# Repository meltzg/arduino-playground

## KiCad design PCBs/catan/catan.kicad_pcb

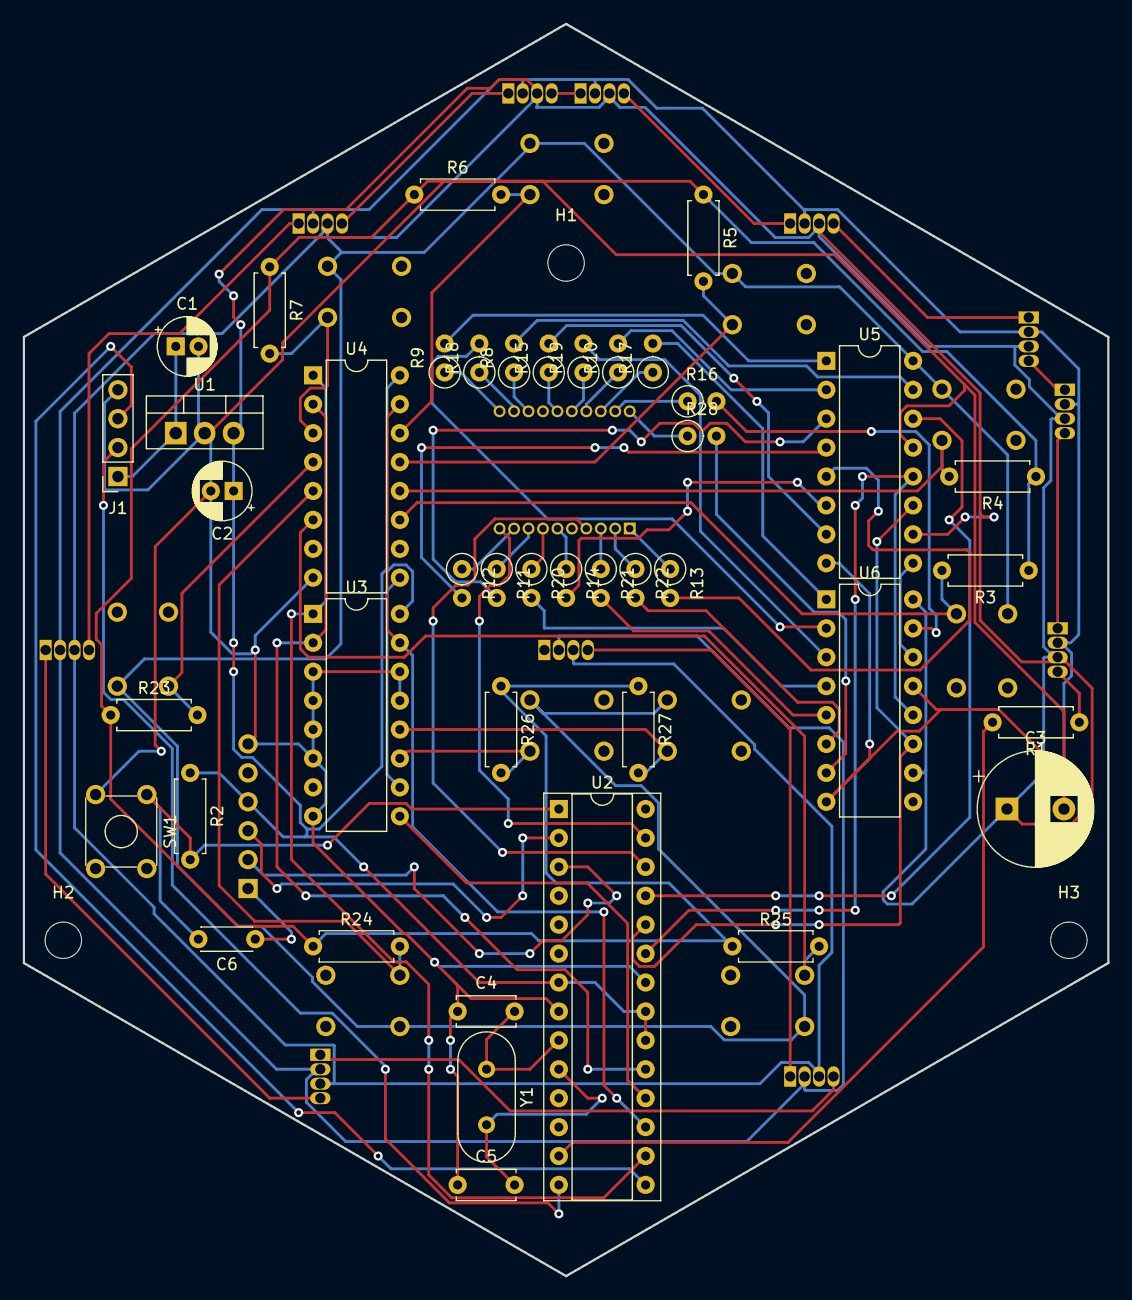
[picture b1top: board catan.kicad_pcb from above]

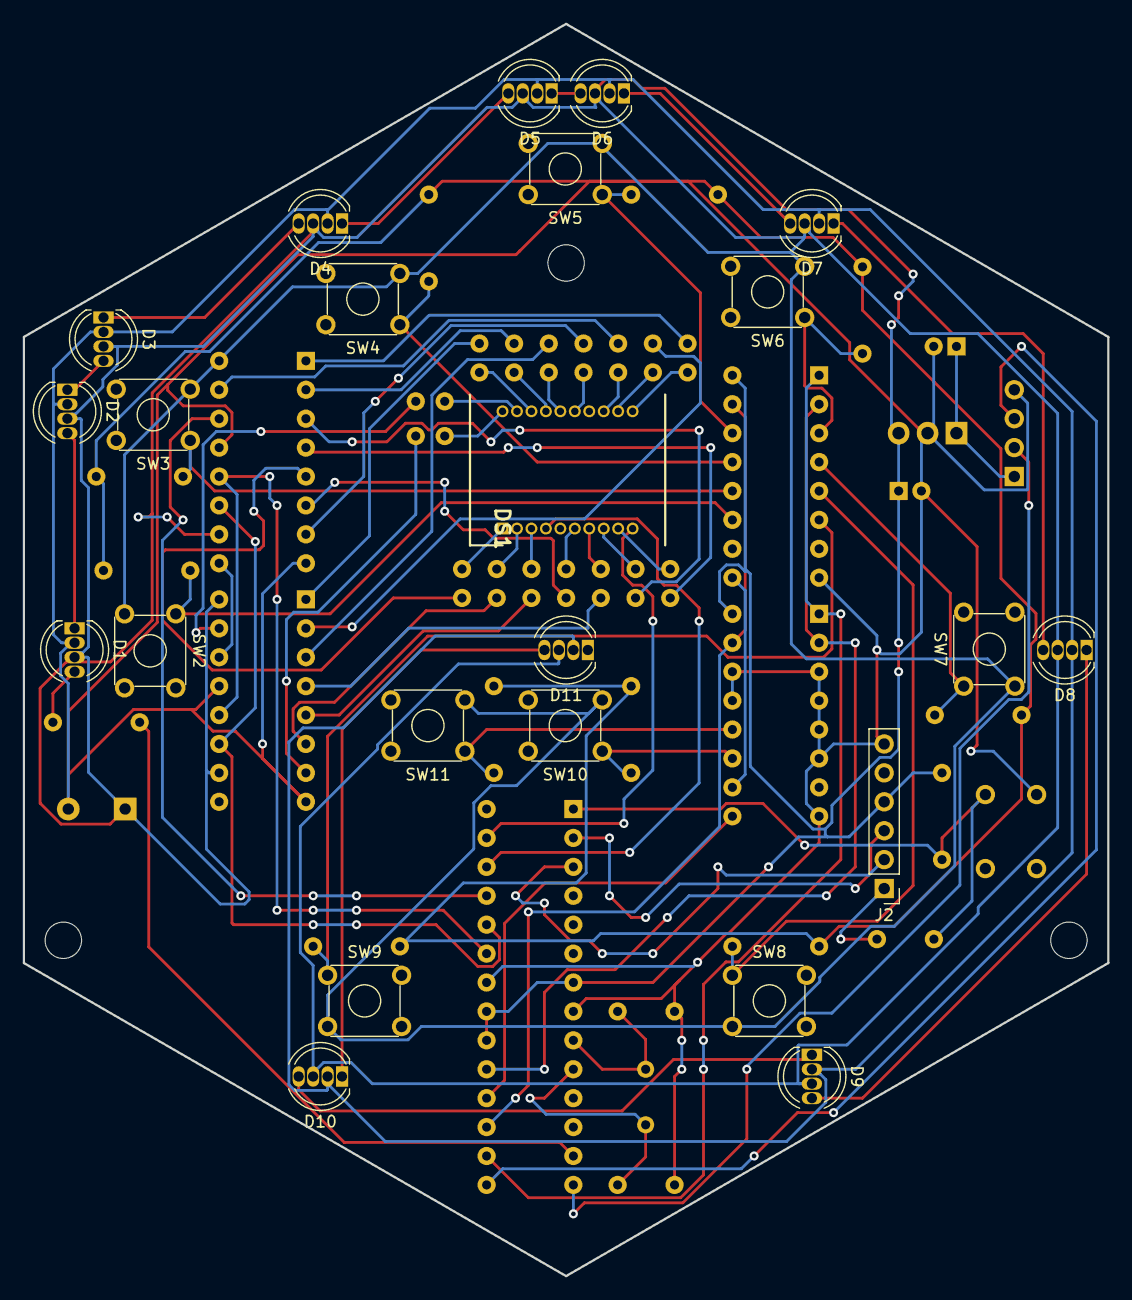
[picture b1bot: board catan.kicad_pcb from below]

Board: 2 copper layers, 95.3 x 110.0 mm, 69 parts (23 on the bottom side), 76 nets.

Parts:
C1, C2: CP1; CP_Radial_D5.0mm_P2.00mm
C3: CP1; CP_Radial_D10.0mm_P5.00mm
C4, C5: C_Small; C_Disc_D5.0mm_W2.5mm_P5.00mm
C6: C_Small; C_Disc_D4.3mm_W1.9mm_P5.00mm
D1, D2, D3, D4, D5, D6, D7, D8, D9, D10, D11: NeoPixel_THT; LED_D5.0mm-4_RGB
DS1: LTP-3862G; DIPS1030W45P127L1690H645Q20N
H1, H2, H3: MountingHole; MountingHole_3.2mm_M3
J1: Conn_01x04_Female; PinSocket_1x04_P2.54mm_Vertical
J2: Conn_01x06_Male; PinHeader_1x06_P2.54mm_Vertical
R1, R2, R3, R4, R5, R6, R7, R23, R24, R25, R26, R27: R; R_Axial_DIN0207_L6.3mm_D2.5mm_P7.62mm_Horizontal
R8, R9, R10, R11, R12, R13, R14, R15, R16, R17, R18, R19, R20, R21, R22, R28: R; R_Axial_DIN0207_L6.3mm_D2.5mm_P2.54mm_Vertical
SW1, SW2, SW3, SW4, SW5, SW6, SW7, SW8, SW9, SW10, SW11: SW_MEC_5E; SW_TH_Tactile_Omron_B3F-10xx
U1: LM7805_TO220; TO-220-3_Vertical
U2: ATmega328P-PU; DIP-28_W7.62mm_Socket
U3, U4: 74HC165; DIP-16_W7.62mm
U5, U6: 74HC595; DIP-16_W7.62mm
Y1: Crystal; Crystal_HC49-4H_Vertical

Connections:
+9V: C1.1, J1.1, U1.1
GND: C1.2, C2.2, C3.2, C4.1, C5.1, D1.2, D2.2, D3.2, D4.2, D5.2, D6.2, D7.2, D8.2, D9.2, D10.2, D11.2, J1.4, J2.6, R3.1, R4.1, R5.1, R6.1, R7.1, R23.1, R24.1, R25.1, R26.1, R27.1, SW1.3, U1.2, U2.8, U2.22, U3.3, U3.4, U3.5, U3.6, U3.8, U3.13, U3.14, U4.8, U5.8, U5.13, U6.8, U6.13
unnamed: C2.1, C3.1, D1.3, D2.3, D3.3, D4.3, D5.3, D6.3, D7.3, D8.3, D9.3, D10.3, D11.3, J2.4, R2.1, SW2.3, SW3.3, SW4.3, SW5.3, SW6.3, SW7.3, SW8.3, SW9.3, SW10.3, SW11.3, U1.3, U2.7, U2.20, U2.21, U3.16, U4.16, U5.10, U5.16, U6.10, U6.16
unnamed: C4.2, U2.9, Y1.1
unnamed: C5.2, U2.10, Y1.2
unnamed: C6.1, J2.1
unnamed: C6.2, R2.2, SW1.1, U2.1
unnamed: D1.1, D2.4
unnamed: D1.4, R1.1
unnamed: D2.1, D3.4
unnamed: D3.1, D4.4
unnamed: D4.1, D5.4
unnamed: D5.1, D6.4
unnamed: D6.1, D7.4
unnamed: D7.1, D8.4
unnamed: D8.1, D9.4
unnamed: D10.1, D11.4
unnamed: D9.1, D10.4
unnamed: DS1.1, R13.1
unnamed: DS1.2, R22.1
unnamed: DS1.3, R21.1
unnamed: DS1.4, U2.26
unnamed: DS1.6, R14.1
unnamed: DS1.7, R20.1
unnamed: DS1.8, R11.1
unnamed: DS1.9, R12.1
unnamed: DS1.10, U2.27
unnamed: DS1.11, R9.1
unnamed: DS1.12, R18.1
unnamed: DS1.13, R8.1
unnamed: DS1.15, R15.1
unnamed: DS1.16, R19.1
unnamed: DS1.17, R10.1
unnamed: DS1.18, R17.1
unnamed: DS1.19, R16.1
unnamed: DS1.20, R28.1
unnamed: J1.2, U2.14
unnamed: J1.3, U2.15
unnamed: J2.2, U2.3
unnamed: J2.3, U2.2
unnamed: R1.2, U2.13
unnamed: R3.2, SW2.1, U4.11
unnamed: R4.2, SW3.1, U4.12
unnamed: R5.2, SW4.1, U4.13
unnamed: R6.2, SW5.1, U4.14
unnamed: R7.2, SW6.1, U4.3
unnamed: R8.2, U5.15
unnamed: R9.2, U5.1
unnamed: R10.2, U5.2
unnamed: R11.2, U5.3
unnamed: R12.2, U5.4
unnamed: R13.2, U5.5
unnamed: R14.2, U5.6
unnamed: R15.2, U5.7
unnamed: R16.2, U6.15
unnamed: R17.2, U6.1
unnamed: R18.2, U6.2
unnamed: R19.2, U6.3
unnamed: R20.2, U6.4
unnamed: R21.2, U6.5
unnamed: R22.2, U6.6
unnamed: R23.2, SW7.1, U4.4
unnamed: R24.2, SW8.1, U4.5
unnamed: R25.2, SW9.1, U4.6
unnamed: R26.2, SW10.1, U3.11
unnamed: R27.2, SW11.1, U3.12
unnamed: R28.2, U6.7
unnamed: U2.16, U3.1, U4.1
unnamed: U2.17, U3.15, U4.15
unnamed: U2.18, U3.9
unnamed: U2.19, U3.2, U4.2
unnamed: U2.23, U5.12, U6.12
unnamed: U2.24, U5.11, U6.11
unnamed: U2.25, U5.14
unnamed: U3.10, U4.9
unnamed: U5.9, U6.14

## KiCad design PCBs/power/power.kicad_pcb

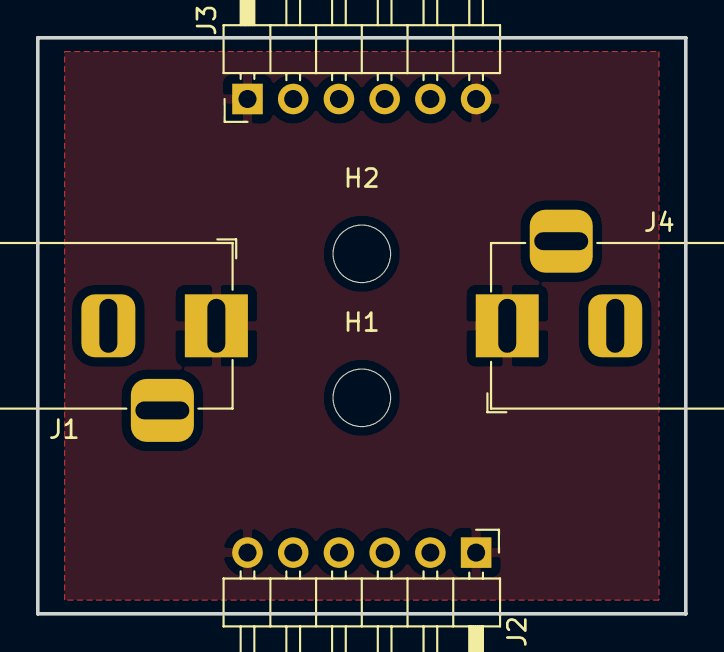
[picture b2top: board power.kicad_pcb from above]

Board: 2 copper layers, 36.0 x 32.0 mm, 6 parts (0 on the bottom side), 2 nets, no tracks yet.

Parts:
H1, H2: MountingHole; MountingHole_3.2mm_M3
J1, J4: Barrel_Jack_Switch; BarrelJack_Horizontal
J2, J3: Conn_01x06_Male; PinHeader_1x06_P2.54mm_Horizontal

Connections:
+9V: J1.1, J2.1, J2.6, J3.1, J3.6, J4.1
GND: J1.2, J2.3, J2.4, J3.3, J3.4, J4.2

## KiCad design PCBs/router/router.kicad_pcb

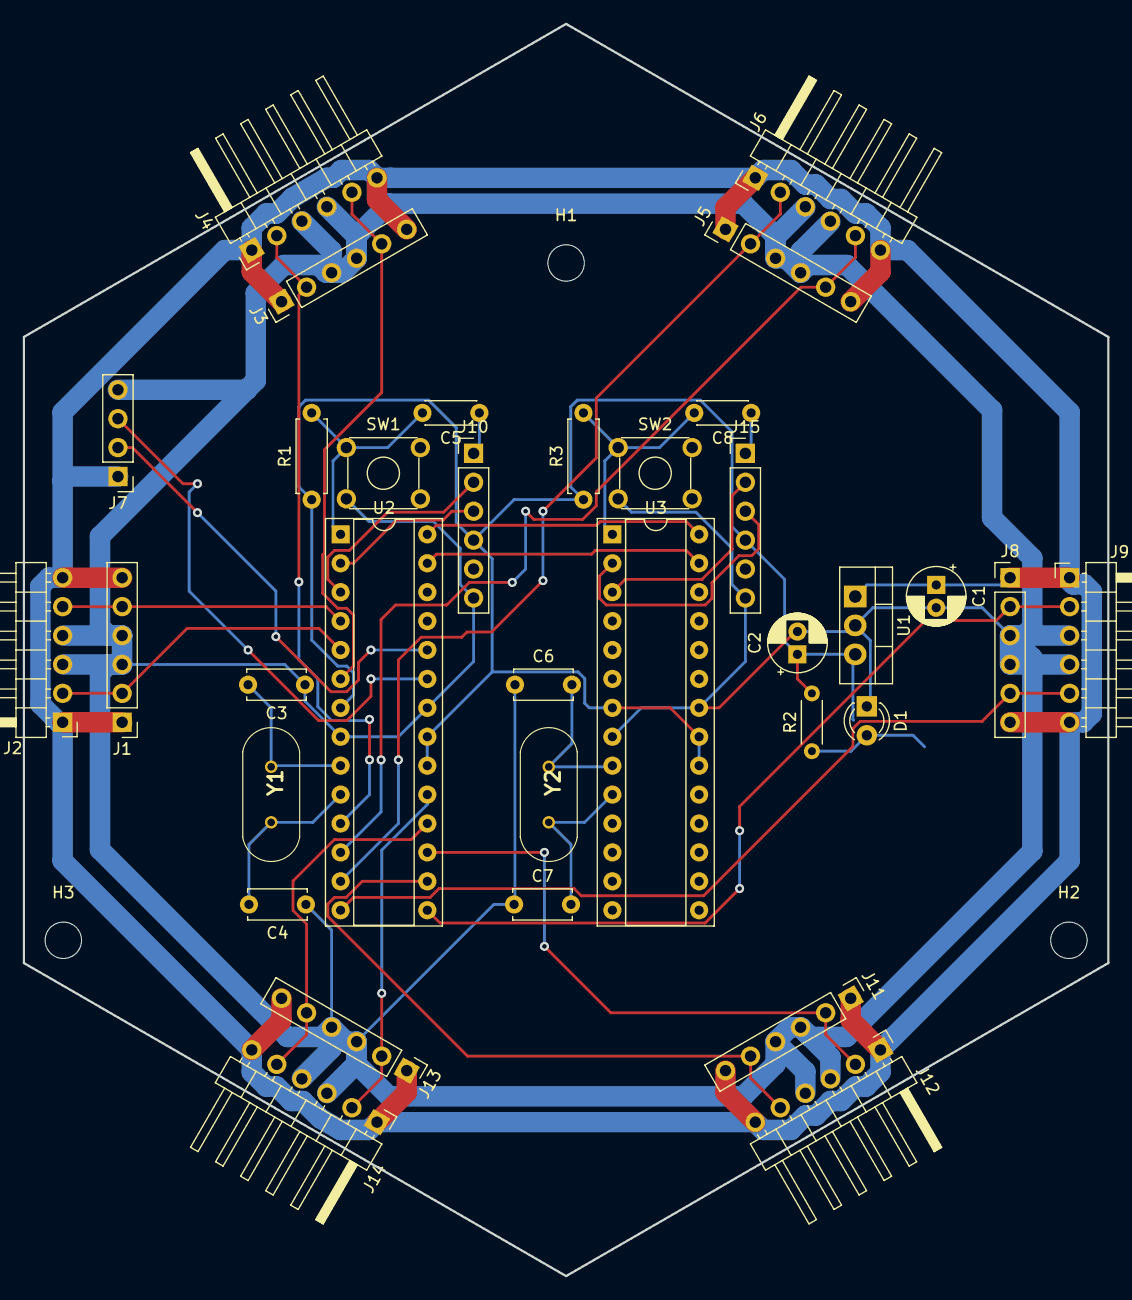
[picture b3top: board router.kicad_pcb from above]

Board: 2 copper layers, 95.3 x 110.0 mm, 37 parts (0 on the bottom side), 32 nets.

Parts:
C1, C2: CP1; CP_Radial_D5.0mm_P2.00mm
C3, C4, C6, C7: C_Small; C_Disc_D5.0mm_W2.5mm_P5.00mm
C5, C8: C_Small; C_Disc_D4.3mm_W1.9mm_P5.00mm
D1: LED; LED_D3.0mm
H1, H2, H3: MountingHole; MountingHole_3.2mm_M3
J1, J3, J5, J8, J10, J11, J13, J15: Conn_01x06_Male; PinHeader_1x06_P2.54mm_Vertical
J2, J4, J6, J9, J12, J14: Conn_01x06_Male; PinHeader_1x06_P2.54mm_Horizontal
J7: Conn_01x04_Male; PinHeader_1x04_P2.54mm_Vertical
R1, R3: R; R_Axial_DIN0207_L6.3mm_D2.5mm_P7.62mm_Horizontal
R2: R; R_Axial_DIN0204_L3.6mm_D1.6mm_P5.08mm_Horizontal
SW1, SW2: SW_MEC_5E; SW_TH_Tactile_Omron_B3F-10xx
U1: LM7805_TO220; TO-220-3_Vertical
U2, U3: ATmega328P-PU; DIP-28_W7.62mm_Socket
Y1, Y2: Crystal; HC_49US__AT49_PTH

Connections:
+9V: C1.1, J1.1, J1.6, J2.1, J2.6, J3.1, J3.6, J4.1, J4.6, J5.1, J5.6, J6.1, J6.6, J7.1, J8.1, J8.6, J9.1, J9.6, J11.1, J11.6, J12.1, J12.6, J13.1, J13.6, J14.1, J14.6, U1.1
GND: C1.2, C2.2, C3.1, C4.1, C6.1, C7.1, D1.1, J1.3, J1.4, J2.3, J2.4, J3.3, J3.4, J4.3, J4.4, J5.3, J5.4, J6.3, J6.4, J7.4, J8.3, J8.4, J9.3, J9.4, J10.6, J11.3, J11.4, J12.3, J12.4, J13.3, J13.4, J14.3, J14.4, J15.6, SW1.3, SW2.3, U1.2, U2.8, U2.22, U3.8, U3.22
unnamed: C2.1, J10.4, J15.4, R1.1, R2.2, R3.1, U1.3, U2.7, U2.20, U2.21, U3.7, U3.20, U3.21
unnamed: C3.2, U2.9, Y1.1
unnamed: C4.2, U2.10, Y1.2
unnamed: C5.1, J10.1
unnamed: C5.2, R1.2, SW1.1, U2.1
unnamed: C6.2, U3.9, Y2.1
unnamed: C7.2, U3.10, Y2.2
unnamed: C8.1, J15.1
unnamed: C8.2, R3.2, SW2.1, U3.1
unnamed: D1.2, R2.1
unnamed: J1.2, J2.2, U2.5
unnamed: J1.5, J2.5, U2.4
unnamed: J3.2, J4.2, U2.11
unnamed: J3.5, J4.5, U2.6
unnamed: J5.2, J6.2, U2.13
unnamed: J5.5, J6.5, U2.12
unnamed: J7.2, U2.24
unnamed: J7.3, U2.23
unnamed: J8.2, J9.2, U2.15
unnamed: J8.5, J9.5, U2.14
unnamed: J10.2, U2.3
unnamed: J10.3, U2.2
unnamed: J11.2, J12.2, U2.17
unnamed: J11.5, J12.5, U2.16
unnamed: J13.2, J14.2, U2.19
unnamed: J13.5, J14.5, U2.18
unnamed: J15.2, U3.3
unnamed: J15.3, U3.2
unnamed: U2.27, U3.27
unnamed: U2.28, U3.28

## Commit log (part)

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2020-11-24 initial network sketch
2020-11-25 set node ID as a 64 bit int
2020-11-26 add protocol info
2020-11-26 almost got message parsing working
2020-11-29 starting work on message processing
2020-12-01 working on get neighbors, but now i need data structures
2020-12-01 rename sketch
2020-12-05 experimenting with neighbors
2020-12-05 some cleanup, neighbor discovery still borked
2020-12-05 Use tmp variable instead of trying ot be smart
2020-12-06 get neighbors works and now uses better wait
2020-12-06 move get neighbors to helper
2020-12-06 use addressable led for status
2020-12-06 reduce node id size to 2 bytes
2020-12-06 probably a mistake, but yeet
2020-12-07 getting closer
2020-12-12 create segment display and put on timer interrupt
2020-12-12 split component into separate files
2020-12-13 forgot to actually add the files
2020-12-13 cleaning up and moving generic messaging out
2020-12-13 working on more shitty data structures
2020-12-13 playing with ds
2020-12-14 bfs is fun
2020-12-14 shortest path finder
2020-12-16 this is going to be rough
2020-12-19 add buttons
2020-12-19 set led based on button press
2020-12-19 correctly set lights for roads and settlements
2020-12-19 set resource colors
2020-12-19 add brightness control
2020-12-19 move updaters to helpers
2020-12-19 use ownership arrays
2020-12-20 render player selection
2020-12-20 rearange pins
2020-12-20 formatting
2020-12-20 new command constants
2020-12-20 add add node command
2020-12-20 remove unused parameter
2020-12-21 remove status led
2020-12-21 start discovery
2020-12-21 send add node messages
2020-12-21 make land color random
2020-12-22 make message a struct
2020-12-22 add discovery stats command
2020-12-24 move common libraries out and chaning graph to have a smaller memory footprint
2020-12-25 changing up some DS
2020-12-25 graph iterator working again
2020-12-25 still using too much memory?
2020-12-26 remove dist
2020-12-26 extract getAdjacent
2020-12-26 pathfinder works great with eeprom edge storage
2020-12-26 try adjusting router to use eeprom based graph. still not enough memory, need pathfinder
2020-12-28 check existing edges in eeprom before adding duplicate
2020-12-28 add void type pathfinder commands
2020-12-28 get discovery stats working
2021-01-01 shortest path doesn't work on the arduino?
2021-01-01 start debugging
2021-01-02 got one path to work?
2021-01-02 more detailed logging
2021-01-02 pathfinder now has an iterator
2021-01-02 get adjacent works
2021-01-05 need to debug why there's no next neighbor request
2021-01-06 discovery works for 2 nodes
2021-01-07 fix shit after removing unnecessary leds and button
2021-01-22 fix includes
2021-01-24 update python client
2021-01-29 Initial schematic for catan pcb
2021-01-30 add footprints
2021-01-30 change resistor footprints
2021-02-06 initial PCB for catan node
2021-02-07 flip display and interface components to back
2021-02-07 fix button wiring
2021-02-07 remove traces... and fix orientation
2021-02-07 more precise placement of components
2021-02-07 wire buttons
2021-02-07 wire segment display to registers
2021-02-07 wire registers together
2021-02-07 wire actor port
2021-02-08 done with pcb?
2021-02-09 stabalize neighbor retrieval
2021-02-12 replace segment display
2021-02-12 initial work on router circuit
2021-02-12 add ports and hook up to power
2021-02-13 assign footprints
2021-02-13 starting to place things
2021-02-14 wire display on schematic
2021-02-18 yay gerber
2021-02-21 3 node iscovery works, but i need a better way to get it past 3
2021-02-23 add node initialization tracking to pathfinder
2021-02-27 cleanup
2021-02-27 update for 16 segment
2021-02-27 reformat
2021-02-28 get things working with common anode and 16 seg
2021-02-28 add scrolling
2021-03-01 add missing ties
2021-03-05 add edges and update footprints
2021-03-05 set connector locations
2021-03-05 place inner ring
2021-03-05 place actor port
2021-03-05 add mounting holes
2021-03-05 and holes for router
2021-03-05 power bus
2021-03-05 complete traces
2021-03-05 update gerber settings
2021-03-13 simple component tester
2021-03-14 move actor port and power regulator
2021-03-20 move user listener out of neighbor loop
2021-03-21 having trouble waiting for messages
2021-03-22 try echoing
2021-03-22 use a statuc message and get colors working right
2021-03-23 pretty good network tester
2021-03-24 make response processing async
2021-03-24 centralize baud for soft serial and settle on a single soft ser lib
2021-04-02 add magnet notches
2021-04-03 widen magnet bracket
2021-04-12 magnet wells
2021-04-15 back to notches
2021-04-16 go back to wider notches
2021-04-16 replace resistor footprints and redo traces
2021-04-17 create top
2021-04-17 shorten lid
2021-04-18 case seems done
2021-04-20 make modes cycle
2021-04-23 shuffle resistors
2021-04-25 trying to make classes for each mode
2021-04-26 indentation
2021-04-26 componentize network test
2021-04-29 cleaning some traces
2021-04-29 some more work on catan mode
2021-05-01 save memory and get roads to render
2021-05-02 wrap string pints in F
2021-05-02 add settlement setting
2021-05-02 add the robber
2021-05-03 add player selection
2021-05-03 --amend
2021-05-04 start on naive catan node setup
2021-05-05 complete naive setup
2021-05-08 send road to neighbor
2021-05-11 move catan state into separate struct
2021-05-11 abstracting catan messages
2021-05-11 wider standoffs
2021-05-12 add placement validation info to state response. keep async state in state requests
2021-05-12 tostring for land
2021-05-12 power port pcb
2021-05-20 go back to original catan layout
2021-05-20 make power pcb bigger
2021-05-22 geber settings
2021-05-25 add settlement reconciliation
2021-05-29 random land with proper ratio
2021-06-01 working on road placement
2021-06-18 oops
2021-06-23 trying not to rely on a separate initialization set
2021-06-23 getting closer to discovering discovery weirdness
2021-07-11 rename network tester methods
2021-07-11 expand router commands
2021-07-11 add discovery stats display to net test
2021-07-14 cleanup some logging
2021-07-22 simplify serialization and use constructors
2021-07-23 commands don't overlap, so no need for bitwise commands. separate options from commands
2021-07-25 update mode messages to have mode IDs
2021-07-25 make network discovery test wake al nodes
2021-08-01 add notches to bottom
2021-08-05 add burn-bootloader to make
2021-08-05 add delays before starting and start all leds off
2021-08-05 move discovery into mode
2021-08-12 cleanup discovery mode
2021-08-12 catan mode is stunted, but master can derive what board should be
2021-08-16 add broadcast to router
2021-08-16 remove unneeded network call
2021-08-17 don't send nwtwork wake in catan
2021-08-17 fix settlement validation
2021-08-19 setup desert tiles
2021-08-20 get player setting working
2021-08-20 groundwork for setting harbors
2021-09-12 take 2 at removing mode oop
2021-09-12 well catan buttons don't work
2021-09-12 fix catan buttons
2021-09-12 broadcast clear robber
2021-09-18 make ID retrieval async
2021-09-18 fix goof with initial catan state id
2021-09-19 lower weight when random land type is selected
2021-09-19 only broadcast player if changed
2021-09-20 get ocean set
2021-09-20 dynamic tile weights
2021-09-20 proper port assignment
2021-09-27 make neighbors part of catanstate
2021-09-27 make a wait command for eeprom clear
2021-09-27 create separate play state type and move neighbors and play status there
2021-09-28 state is saved, but network is gone
2021-09-28 long press land btn to restart/rediscover
2021-09-29 turn harbors back on
2021-10-11 repeat complete method
2021-10-12 update protocol header definition
2021-10-14 router wasn't clearing topology correctly
2021-10-15 reenable catan
2021-10-15 create standoff test tool
2021-10-16 update new player correctly
2021-10-16 changes to enclosure
2021-10-17 make harbor count based on num land
2021-10-17 fix lower limit for harbors
2021-10-18 change top to have no walls
2021-10-25 no robber rolls
2021-11-16 add complete retries to all messages in catan
2021-11-18 flip programmer connector
2021-11-21 redo settlement placement
2021-12-28 make router push discovery stat updates
2021-12-28 Revert "make sure only 1 node is sending messages during discovery test"
    This reverts commit 27ee15b183985cf00f4e6097f072f882356f8bcf.
2021-12-28 don't display neighbor IDs
2021-12-28 fix new game
2021-12-28 make it possible to rediscover
2021-12-28 add new game without rediscovery (#3)
    * add new game without rediscovery
    * fix new game
    * make it possible to rediscover
2022-01-12 slow soft baud more
2022-01-12 make reset neighbors return if there are none
2022-01-17 use static array for harborTiles and desertTiles
2022-01-28 make python helper useful
2022-01-29 create better CLI tool for interacting with network
2022-01-29 playing with pathfinder
2022-01-29 format message better
2022-01-29 clean up tester and slow down i2c
2022-01-29 reduce pathfinder usage
2022-01-30 cleanup and logging
2022-01-30 remove timeout stuff
2022-01-30 cleans
2022-02-01 make set ID sketch
2022-02-01 make ID 1 byte
2022-02-01 create script to set IDs in bulk
2022-02-03 update ids
2022-02-10 update latest ID
2022-02-10 set player on initialization to 0
2024-02-25 almost able to generate graph
2024-02-25 fix neighbor calculation
2024-02-26 fix neighbor calculation for real this time
2024-02-27 almost able to render a hex graph correctly
2024-02-27 not working, but matches my expected logic?
2024-02-28 switch to doubled coordinate system instead of butchered axial/offset
2024-02-28 render ports
2024-02-28 move port render into separate function
2024-02-28 add text to port
2024-02-29 draw-board should do the superimposition
2024-03-01 add robber rendering
2024-03-02 assign harbors
2024-03-02 assign land values
2024-03-02 draw settlements and roads
2024-03-02 use map to represent road
2024-03-03 add more details in setup-game
2024-03-03 starting with settlement validation and placement
2024-03-03 draw pieces on top
2024-03-03 add function to get all available settlement locations
2024-03-04 assign initial settlement
2024-03-04 make the graph in game state a map
2024-03-08 settlement placement and validation for normal game time
2024-03-08 check if road is already owned
2024-03-08 extract initial settlement selection function and remove initial road selection
2024-03-08 draw basic player stats
2024-03-08 add structures to player stats
2024-03-09 change initial setup so that it can run in a game loop
2024-03-11 move the robber, discard, and collect resources
2024-03-14 helpers for taking actions
2024-03-14 valid-settlement? needs post setup phase validation
2024-03-15 valid-settlement? can validate after setup
2024-03-16 implement port resource substitutions
2024-03-16 remove settlement when building city
2024-03-16 Game loop (#5)
    * change initial setup so that it can run in a game loop
    * collect resources
    * move the robber, discard, and collect resources
    * helpers for taking actions
    * valid-settlement? needs post setup phase validation
    * valid-settlement? can validate after setup
2024-03-20 comm constants
2024-03-24 not sure where the payload is going
2024-03-24 sending and recieving messages!
2024-03-28 initial attempt at hardware serial proxy
2024-03-31 attempt at hardware proxy
2024-03-31 differentiate hardware proxy request and response
2024-04-01 send discovery stats to port h if hardware proxy request
2024-04-02 get discovery stats working with remote requests
2024-04-03 split serial from router specific functions
2024-04-05 add some structs for new commands
2024-04-08 get set-state working
2024-04-12 get acknowledgement working
2024-04-12 send neighbor set road commands during set state
2024-04-13 remove unneeded logs
2024-04-15 add get playstate command
2024-04-20 add wake node command
2024-04-20 trying to get it to play a game
2024-04-21 make update wait for ack and create main loop script
2024-04-22 the board needs to know which roads are valid for the set tile message
